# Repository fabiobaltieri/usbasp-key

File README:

USBASP KEY
==========

This project is an AVR ISP programmer with USB interface in a compact usb
key PCB. The project is based on the original USBasp version of Thomas Fischl,
which can be found on:

http://www.fischl.de/usbasp/

License
-------

This program is free software: you can redistribute it and/or modify
it under the terms of the GNU General Public License as published by
the Free Software Foundation, either version 2 of the License, or
(at your option) any later version.

Contents
--------

COPYING     text version of the GPL
README      this file
firmware/   source directory for firmware files
hardware/   source directory for the hardware design files

Firmware
--------

Building requires an avr-gcc toolchain, in the firmware/ directory, to build
run:

  make main.hex

Flashing the firmware on the device requires avrdude and a compatible hardware
programmer. Default configuration is stored at the beginning of the Makefile.
To program with the default configuration, run:

  make flash

Fuses can be configured running:

  make fuses

Hardware
--------

All hardware files (schematic, layout and libraries) are in CadSoft Eagle
format.

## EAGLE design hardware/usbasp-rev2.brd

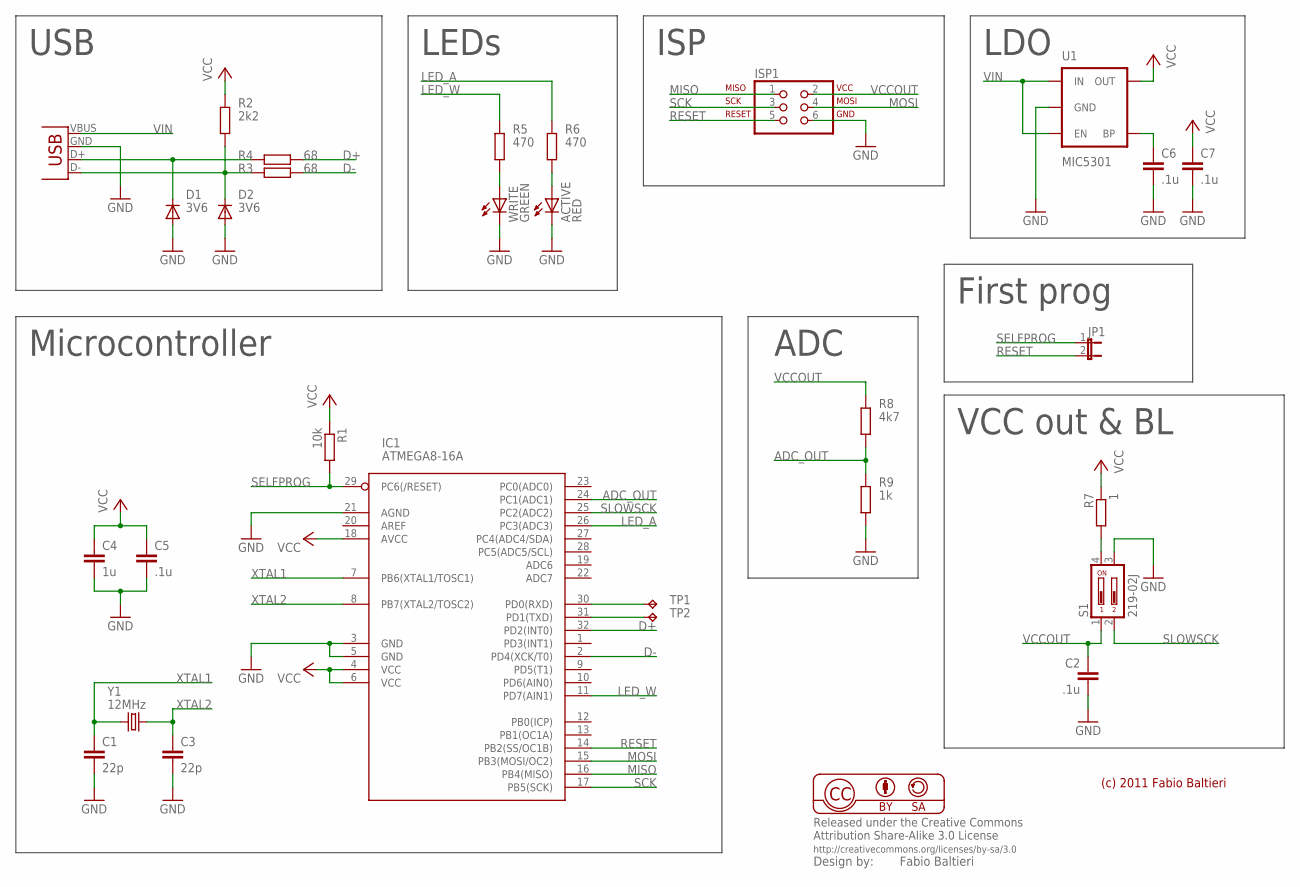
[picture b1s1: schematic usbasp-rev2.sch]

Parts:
ACTIVE: RED; CHIP-LED0805
C1, C3: 22p; C0603
C2, C5, C6, C7: .1u; C0603
C4: 1u; C0603
D1, D2: 3V6; SMA-DIODE
IC1: ATMEGA8-16A; TQFP32-08
ISP1: ISP-AVR910SMD; 2X03_BORDER
JP1: JUMPER-2SMD-NO-NS; SJ_2S-NO-NS
R1: 10k; R0603
R2: 2k2; R0603
R3, R4: 68; R0603
R5, R6: 470; R0603
R7: 1; R0805
R8: 4k7; R0603
R9: 1k; R0603
S1: 219-02J; CTS-219-02J
TP1, TP2: TPB1,27; B1,27
U1: MIC5301; SOT23-5
WRITE: GREEN; CHIP-LED0805
X1: USB-A-H
Y1: 12MHz; CRYSTAL-SMD-5X3

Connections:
ADC_OUT: IC1.24 (PC1(ADC1)), R8.2, R9.1
D+: IC1.32 (PD2(INT0)), R4.1
D-: IC1.2 (PD4(XCK/T0)), R3.1
GND: ACTIVE.C, C1.1, C2.2, C3.1, C4.2, C5.2, C6.2, C7.2, D1.A, D2.A, IC1.3 (GND), IC1.5 (GND), IC1.21 (AGND), ISP1.6, R9.2, S1.3, U1.2 (GND), WRITE.C, X1.GND (VBUS)
LED_A: IC1.26 (PC3(ADC3)), R6.1
LED_W: IC1.11 (PD7(AIN1)), R5.1
MISO: IC1.16 (PB4(MISO)), ISP1.1
MOSI: IC1.15 (PB3(MOSI/OC2)), ISP1.4
unnamed: C6.1, U1.4 (BP)
unnamed: R5.2, WRITE.A
unnamed: D1.C, R4.2, X1.D+ (D-)
unnamed: D2.C, R2.1, R3.2, X1.D- (D+)
unnamed: ACTIVE.A, R6.2
unnamed: IC1.30 (PD0(RXD)), TP1.TP
unnamed: R7.2, S1.4
unnamed: IC1.31 (PD1(TXD)), TP2.TP
RESET: IC1.14 (PB2(SS/OC1B)), ISP1.5, JP1.2
SCK: IC1.17 (PB5(SCK)), ISP1.3
SELFPROG: IC1.29 (PC6(/RESET)), JP1.1, R1.2
SLOWSCK: IC1.25 (PC2(ADC2)), S1.2
VCC: C4.1, C5.1, C7.1, IC1.4 (VCC), IC1.6 (VCC), IC1.18 (AVCC), R1.1, R2.2, R7.1, U1.5 (OUT)
VCCOUT: C2.1, ISP1.2, R8.1, S1.1
VIN: U1.1 (IN), U1.3 (EN), X1.VBUS (GND)
XTAL1: C1.2, IC1.7 (PB6(XTAL1/TOSC1)), Y1.1
XTAL2: C3.2, IC1.8 (PB7(XTAL2/TOSC2)), Y1.3 (2)

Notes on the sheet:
(c) 2011 Fabio Baltieri
Microcontroller
USB
LEDs
ISP
First prog
VCC out & BL
LDO
ADC

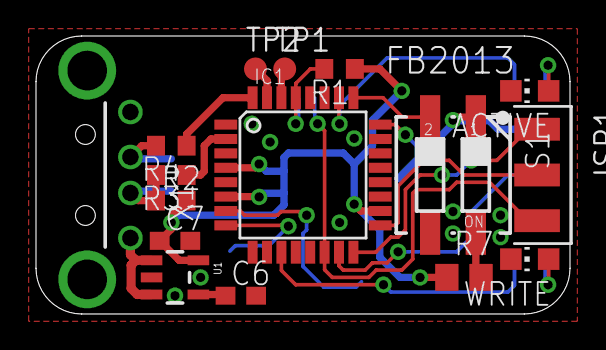
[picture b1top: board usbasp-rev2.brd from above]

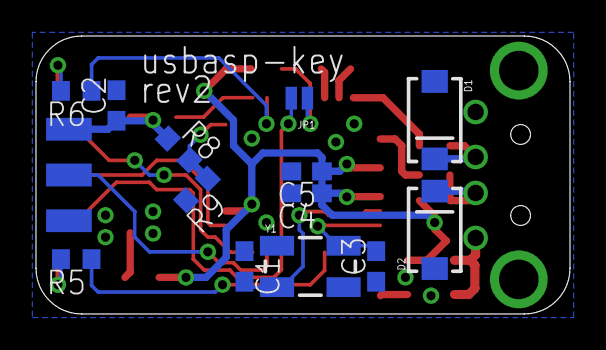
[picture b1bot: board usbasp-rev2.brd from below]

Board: 2 copper layers, 29.7 x 15.4 mm, 29 parts (13 on the bottom side), 25 nets.

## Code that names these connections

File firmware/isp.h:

/*
 * Copyright 2011 Fabio Baltieri (fabio.baltieri@gmail.com)
 *
 * Based on the original USBasp code written by
 *   Thomas Fischl <tfischl@gmx.de>, Copyright 2005
 *
 * This program is free software: you can redistribute it and/or modify
 * it under the terms of the GNU General Public License as published by
 * the Free Software Foundation, either version 3 of the License, or
 * (at your option) any later version.
 *
 */

#ifndef __isp_h_included__
#define	__isp_h_included__

#ifndef uchar
#define	uchar	unsigned char
#endif

#define	ISP_OUT   PORTB
#define ISP_IN    PINB
#define ISP_DDR   DDRB
#define ISP_RST   PB2
#define ISP_MOSI  PB3
#define ISP_MISO  PB4
#define ISP_SCK   PB5

/* Prepare connection to target device */
void ispConnect();

/* Close connection to target device */
void ispDisconnect();

/* read an write a byte from isp using software (slow) */
uchar ispTransmit_sw(uchar send_byte);

/* read an write a byte from isp using hardware (fast) */
uchar ispTransmit_hw(uchar send_byte);

/* enter programming mode */
uchar ispEnterProgrammingMode();

/* read byte from eeprom at given address */
uchar ispReadEEPROM(unsigned int address);

/* write byte to flash at given address */
uchar ispWriteFlash(unsigned long address, uchar data, uchar pollmode);

uchar ispFlushPage(unsigned long address, uchar pollvalue);

/* read byte from flash at given address */
uchar ispReadFlash(unsigned long address);

/* write byte to eeprom at given address */
uchar ispWriteEEPROM(unsigned int address, uchar data);

/* pointer to sw or hw transmit function */
uchar (*ispTransmit)(uchar);

/* set SCK speed. call before ispConnect! */
void ispSetSCKOption(uchar sckoption);

#endif /* __isp_h_included__ */

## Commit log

2011-08-20 firmware: initial import of original usbasp 2009-10-23 firmware
    This is an import of the original firmware found on:
    http://www.fischl.de/usbasp/
2011-08-20 Makefile: changed target to atmega168
2011-08-20 clock.h: removed F_CPU define (is now in Makefile)
2011-08-20 usbconfig.h: changed soft-usb data pins to PD4 and PD2
2011-08-20 rewritten gpio intialization to support usbasp-key version
2011-08-20 changed file format from dos to unix
2011-08-20 hardware: imported hardware files
2011-08-20 COPYING: added complete GPLv2 text
2011-08-20 added README file
2011-08-20 hardware: added copyright text
2011-08-20 added .gitignore file
2011-09-02 README: changed to markdown format
2011-09-05 hardware: added schematics in pdf version
2011-11-20 Update copyright information
2011-11-20 LICENSE: update to gplv3
2011-11-20 hardware: add CC BY-SA license
2012-01-13 binaries: add pre-built firmware images
2012-01-13 README: update contents list
2012-01-23 hardware: convert files to eagle v6 format (xml)
2012-01-23 hardware: coscmetic fixes
2012-03-03 bootloader: add original bootloadHID firmware
2012-03-03 bootloader: Makefile: set fuse for ATmega168
2012-03-03 bootloader: setup for ATmega168 on usbasp board
2012-03-03 bootloader: change hfuse to 0xdd (3v3 BOD)
2012-03-03 usbdrv: update to latest usbdrv sources
2012-03-03 main: change init sequence for correct usb reset
2012-03-03 main: blink led on init while waiting
2012-05-25 README: add project homepage link
2012-11-24 hw: add rev2
2012-11-30 hw: updated rev2 schematics
2012-11-30 hw: rev2: fix ldo part number
2012-11-30 hw: rev2: add silkscreen
2013-01-20 hw: happy 2013
2013-03-17 hw: update part values
2013-03-17 fw/bootloader: update vusb library
2013-03-17 fw: update leds to rev2 hardware

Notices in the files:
parts and their libraries:
SparkFun-PowerIC: Licensing: CC v3.0 Share-Alike You are welcome to use this library for commercial purposes.
balto: Released under the Creative Commons
balto: http://creativecommons.org/licenses/by-sa/3.0
